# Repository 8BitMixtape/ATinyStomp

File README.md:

# ATinyStomp

## KiCAD version of 8Bit Mixtape

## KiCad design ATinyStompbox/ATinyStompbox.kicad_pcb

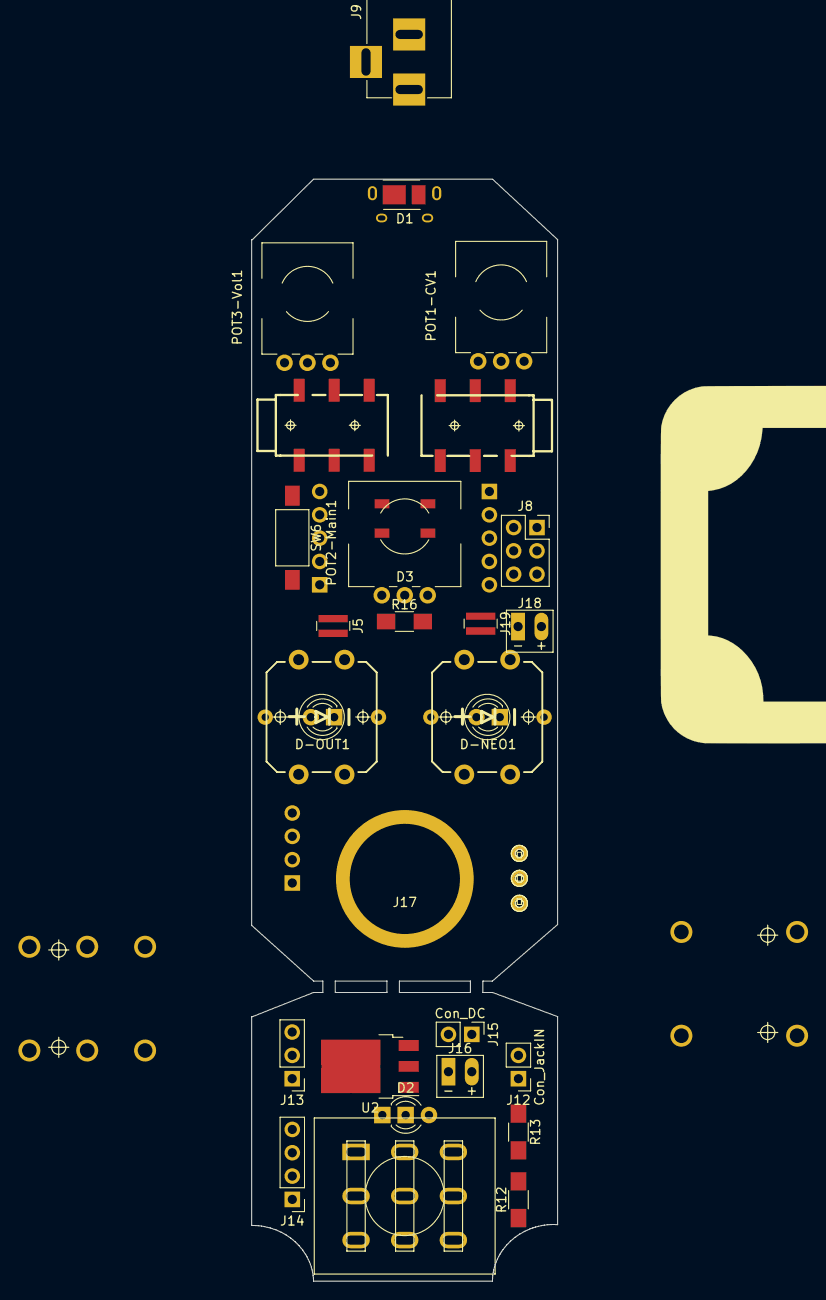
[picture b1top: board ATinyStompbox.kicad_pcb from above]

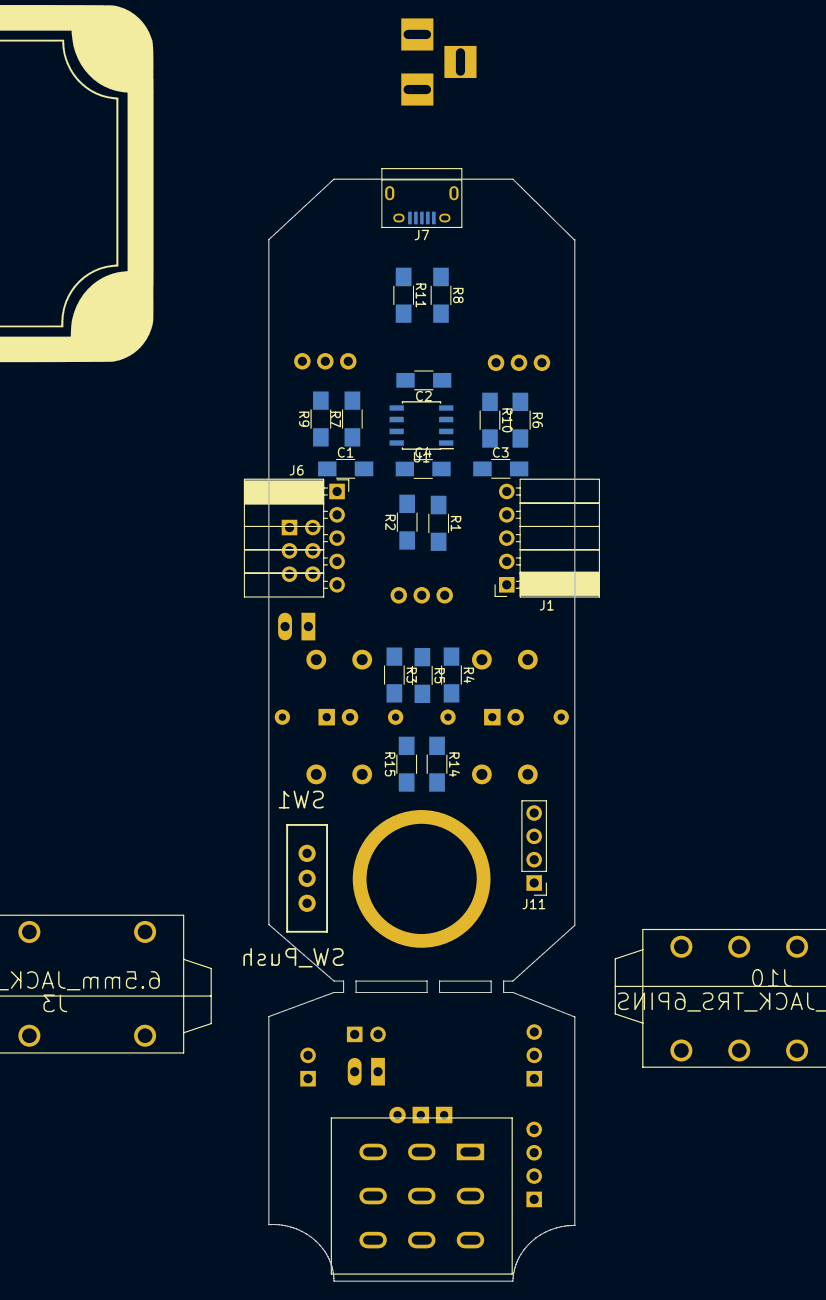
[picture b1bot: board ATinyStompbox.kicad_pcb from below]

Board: 2 copper layers, 33.3 x 120.0 mm, 56 parts (22 on the bottom side), 34 nets, no tracks yet.

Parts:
C1, C2, C3: 100nF; C_1206_HandSoldering
C4: 10uF; C_1206_HandSoldering
D1: LED; LED_PLCC_2835_Handsoldering
D2: LED_Dual_CCA; Stomp_LED-Ring_DUAL
D3: LED_NEO; Mixtape_NEO_WS2812B
D-NEO1: LED; LED_D3.0mm
D-OUT1: LED; LED_D3.0mm
J1, J6: CONN_01X05; Socket_Strip_Angled_1x05_Pitch2.54mm
J2, J4: JACK_TRS_6PINS; AUDIO-JACK-TRS-SMD
J3: 6.5mm_JACK_3P; AUDIO-6.5mm-JACK_Mono_switched
J5, J19: CONN_01X02_MALE; R_0612
J7: USB_OTG; USB_Micro-B
J8: CONN_02X03; Socket_Strip_Straight_2x03_Pitch2.54mm
J9: BARREL_JACK; 9V_BARREL_JACK
J10: 6.5mm_JACK_TRS_6PINS; AUDIO-6.5mm-JACK_Stereo_switched
J11, J14: CONN_01X04; Socket_Strip_Straight_1x04_Pitch2.54mm
J12: Con_JackIN; Socket_Strip_Straight_1x02_Pitch2.54mm
J13: Con_JackOUT; Socket_Strip_Straight_1x03_Pitch2.54mm
J15: Con_DC; Socket_Strip_Straight_1x02_Pitch2.54mm
J16: Con_BAT; Bat_connector
J17: StompDrillHole; StompLoch
J18: Con_3-5V; Bat_connector
J20: BoardDimension; CaseDim
J21: FullDimension; StompCase_Full
POT1-CV1: POT 10K lin; Mixtape_Pot_Alps_RK09K_Horizontal
POT2-Main1: POT 10K lin Sleeve; Mixtape_Pot_Alps_RK09L_Sleve_Single_Horizontal
POT3-Vol1: POT 10k; Mixtape_Pot_Alps_RK09K_Horizontal
R1, R2, R3, R4, R5: 22k; R_1206_HandSoldering
R6, R7: 22K; R_1206_HandSoldering
R8, R13, R16: 330; R_1206_HandSoldering
R9, R10, R12: 4.7K; R_1206_HandSoldering
R11, R14, R15: 1K; R_1206_HandSoldering
SW1: SW_Push; SWITCH-SPDT_KIT
SW2, SW3: SW_Push; TACTILE-PTH-LED-12MM
SW5: SW_3PDT; STOMP-SWITCH-3PDT
SW6: SW_Push; SW_SPST_FSMSM
U1: ATTINY85-20SU; SOIC-8_3.9x4.9mm_Pitch1.27mm
U2: 7805; TO-252-3_TabPin2

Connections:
+3V3: J18.2, J19.2, SW1.1
AudioProg: C1.1, J2.3
But-L: R3.2, SW2.1
But-R: R4.2, R5.2, SW3.1
CV_IN: J1.3, J2.2
CV_OUT: C3.1, POT3-Vol1.1, R8.1
DC_in: J9.1, J15.2, J16.2
GND: C2.2, C3.2, C4.2, D3.3, D-NEO1.1, D-OUT1.1, J1.1, J2.1, J3.3, J4.1, J7.5, J7.6, J9.2, J10.1, J11.1, J12.1, J13.1, J14.1, J15.1, J18.1, POT1-CV1.3, POT2-Main1.3, POT3-Vol1.3, R2.2, R11.2, R12.2, R13.2, SW2.2, SW3.2, SW6.2, U1.4
Jack_IN: J3.1, J12.2, SW5.2
Jack_OUT: J10.2, J13.2, SW5.8
Jack_Ring: J10.3, J13.3, J16.1
unnamed: D1.1, R11.1
unnamed: D2.2, SW5.5
unnamed: D3.4, R16.1
unnamed: D-NEO1.2, R15.1
unnamed: D-OUT1.2, R14.2
unnamed: J5.1, SW6.1, U1.1
unnamed: POT1-CV1.2, R7.2
unnamed: POT2-Main1.1, R10.2
unnamed: POT2-Main1.2, R6.2
unnamed: R12.1, SW5.6
unnamed: R13.1, SW5.4
unnamed: SW5.3, SW5.9
PB0: R15.2, R16.2, U1.5
PB1: D2.1, R8.2, R14.1, U1.6
PB2/A1: R7.1, U1.7
PB3: C1.2, R1.2, R2.1, R3.1, R4.1, R5.1, U1.2
PB4/A2: R6.1, U1.3
Sound_IN: J11.3, POT1-CV1.1, R9.2
Sound_OUT: J4.2, J11.4, POT3-Vol1.2
Stomp_from_PCB: J14.4, SW5.7
Stomp_to_PCB: J14.3, SW5.1
Sync_OUT: J4.3, J5.2
VCC: C2.1, C4.1, D1.2, D2.3, D3.1, J1.2, J7.1, J11.2, J19.1, R1.1, R9.1, R10.1, SW1.2, U1.8

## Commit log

2018-07-16 first all current files
2018-07-16 adding extra resources
2018-07-16 photos
2018-07-16 new netlist
2018-07-16 mod readme
2018-07-16 adding schematics
2018-07-26 small improvements
2018-07-26 new schematics for DualLED
